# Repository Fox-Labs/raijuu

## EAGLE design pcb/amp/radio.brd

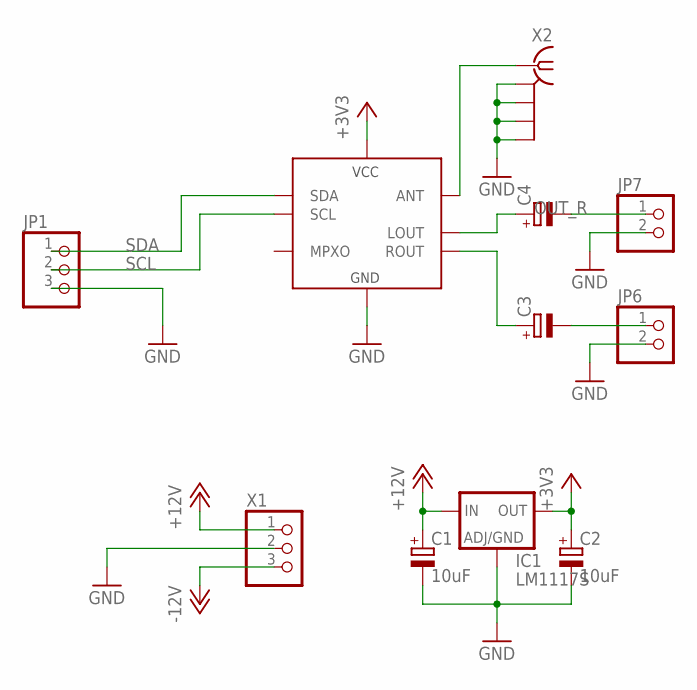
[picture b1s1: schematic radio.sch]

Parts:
C1, C2: 10uF; SMC_A
C3, C4: CPOL-EUD; PANASONIC_D
IC1: LM1117S; SOT223
JP1: PINHD-1X3180; 1X03
JP6, JP7: PINHD-1X2; 1X02
U1: TEA5767
X1: 22-23-2031
X2: BU-SMA-V

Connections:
+3V3: C2.+, IC1.2 (OUT), IC1.4 (OUT), U1.5 (VCC)
+12V: C1.+, IC1.3 (IN), X1.1
-12V: X1.3
GND: C1.-, C2.-, IC1.1 (ADJ), JP1.3, JP6.2, JP7.2, U1.3 (GND), U1.6 (GND), X1.2, X2.2 (GND1), X2.3 (GND2), X2.4 (GND3), X2.5 (GND4)
unnamed: U1.10 (ANT), X2.1
unnamed: C3.+, U1.7 (ROUT)
unnamed: C3.-, JP6.1
unnamed: C4.-, JP7.1
OUT_R: C4.+, U1.8 (LOUT)
SCL: JP1.2, U1.2 (SCL)
SDA: JP1.1, U1.1 (SDA)

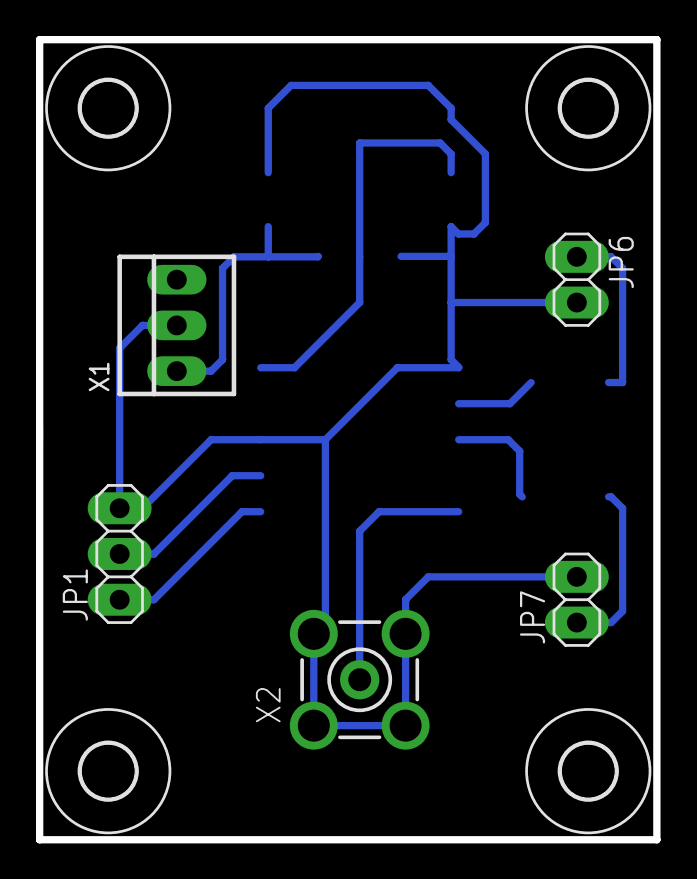
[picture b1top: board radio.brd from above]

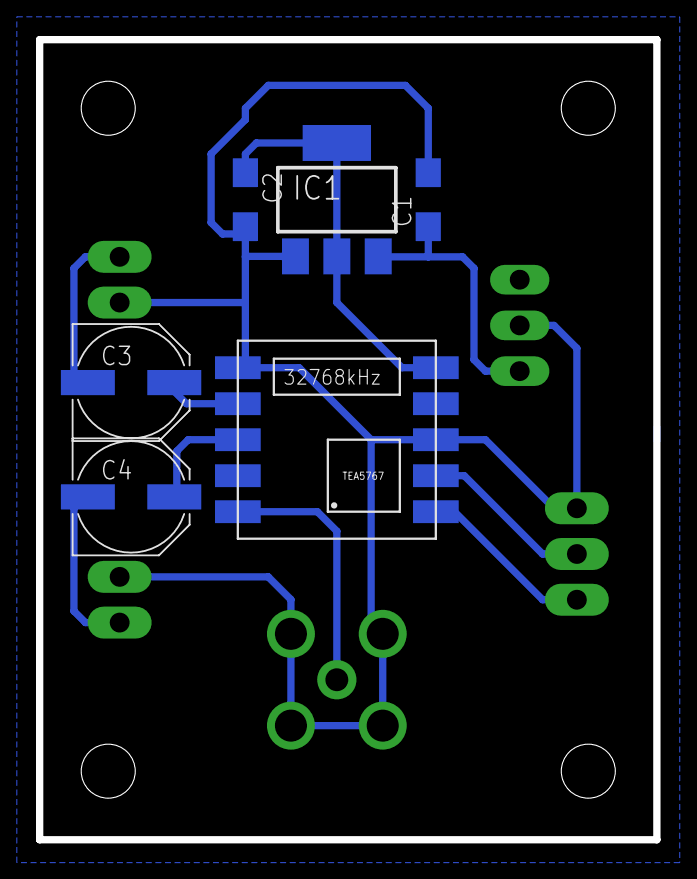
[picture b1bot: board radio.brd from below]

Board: 2 copper layers, 34.3 x 44.5 mm, 15 parts (6 on the bottom side), 10 nets.

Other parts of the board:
U$1, U$2, U$3, U$4: 3,0

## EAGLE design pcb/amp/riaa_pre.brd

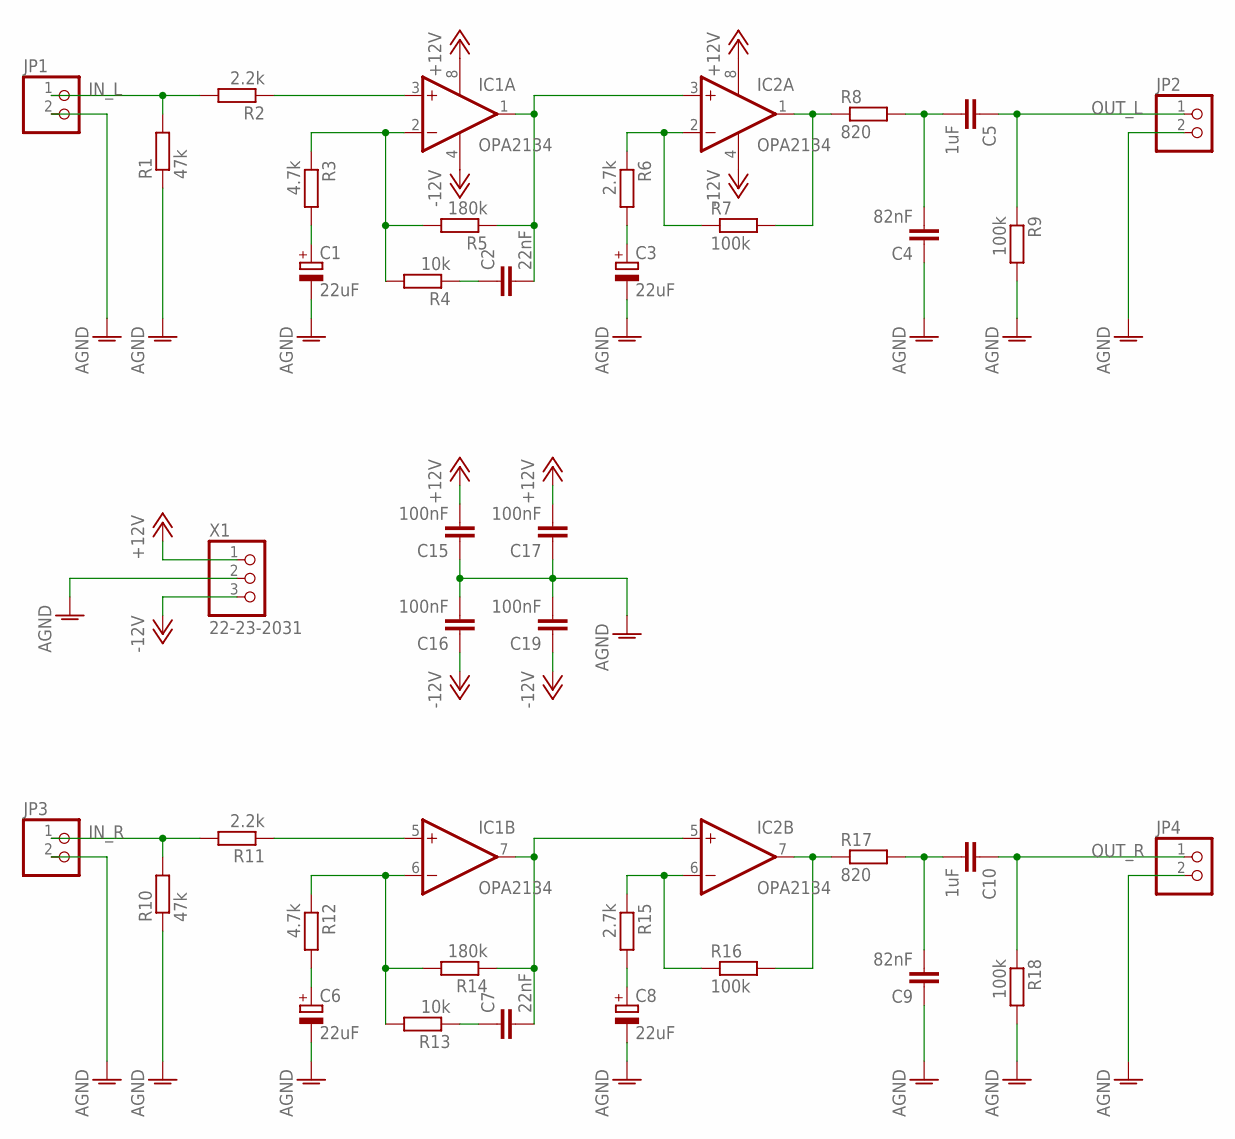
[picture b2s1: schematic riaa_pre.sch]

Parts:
C1, C3, C6, C8: 22uF; E2,5-6
C2, C7: 22nF; C050-025X075
C4, C9: 82nF; C050-025X075
C5, C10: 1uF; C050-045X075
C15, C16, C17, C19: 100nF; C050-025X075
IC1, IC2: OPA2134; DIL08
JP1, JP2, JP3, JP4: PINHD-1X2; 1X02
R1, R10: 47k; 0207/7
R2, R11: 2.2k; 0207/7
R3, R12: 4.7k; 0207/7
R4, R13: 10k; 0207/7
R5, R14: 180k; 0207/7
R6, R15: 2.7k; 0207/7
R7, R9, R16, R18: 100k; 0207/7
R8, R17: 820; 0207/7
X1: 22-23-2031

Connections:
+12V: C15.2, C17.2, IC1.8 (V+), IC2.8 (V+), X1.1
-12V: C16.1, C19.1, IC1.4 (V-), IC2.4 (V-), X1.3
AGND: C1.-, C3.-, C4.1, C6.-, C8.-, C9.1, C15.1, C16.2, C17.1, C19.2, JP1.2, JP2.2, JP3.2, JP4.2, R1.1, R9.2, R10.1, R18.2, X1.2
IN_L: JP1.1, R1.2, R2.2
IN_R: JP3.1, R10.2, R11.2
unnamed: C3.+, R6.2
unnamed: IC1.3 (+IN), R2.1
unnamed: C2.2, IC1.1 (OUT), IC2.3 (+IN), R5.1
unnamed: C4.2, C5.2, R8.2
unnamed: C2.1, R4.1
unnamed: IC1.2 (-IN), R3.1, R4.2, R5.2
unnamed: IC2.6 (-IN), R15.1, R16.1
unnamed: IC2.7 (OUT), R16.2, R17.1
unnamed: IC1.5 (+IN), R11.1
unnamed: C7.2, IC1.7 (OUT), IC2.5 (+IN), R14.1
unnamed: C7.1, R13.1
unnamed: IC1.6 (-IN), R12.1, R13.2, R14.2
unnamed: C6.+, R12.2
unnamed: C8.+, R15.2
unnamed: C9.2, C10.2, R17.2
unnamed: IC2.2 (-IN), R6.1, R7.1
unnamed: IC2.1 (OUT), R7.2, R8.1
unnamed: C1.+, R3.2
OUT_L: C5.1, JP2.1, R9.1
OUT_R: C10.1, JP4.1, R18.1

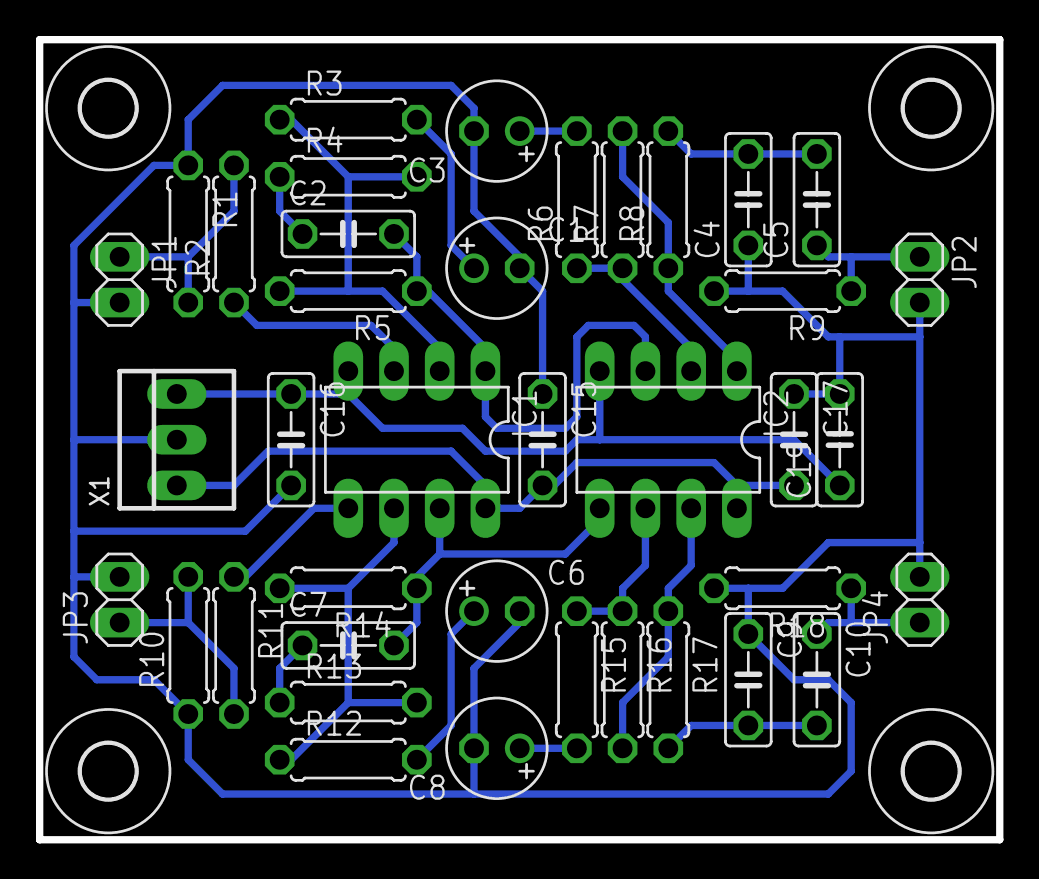
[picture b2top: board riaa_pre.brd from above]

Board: 2 copper layers, 53.3 x 44.5 mm, 43 parts (0 on the bottom side), 25 nets.

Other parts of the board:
U$1, U$2, U$3, U$4: 3,0

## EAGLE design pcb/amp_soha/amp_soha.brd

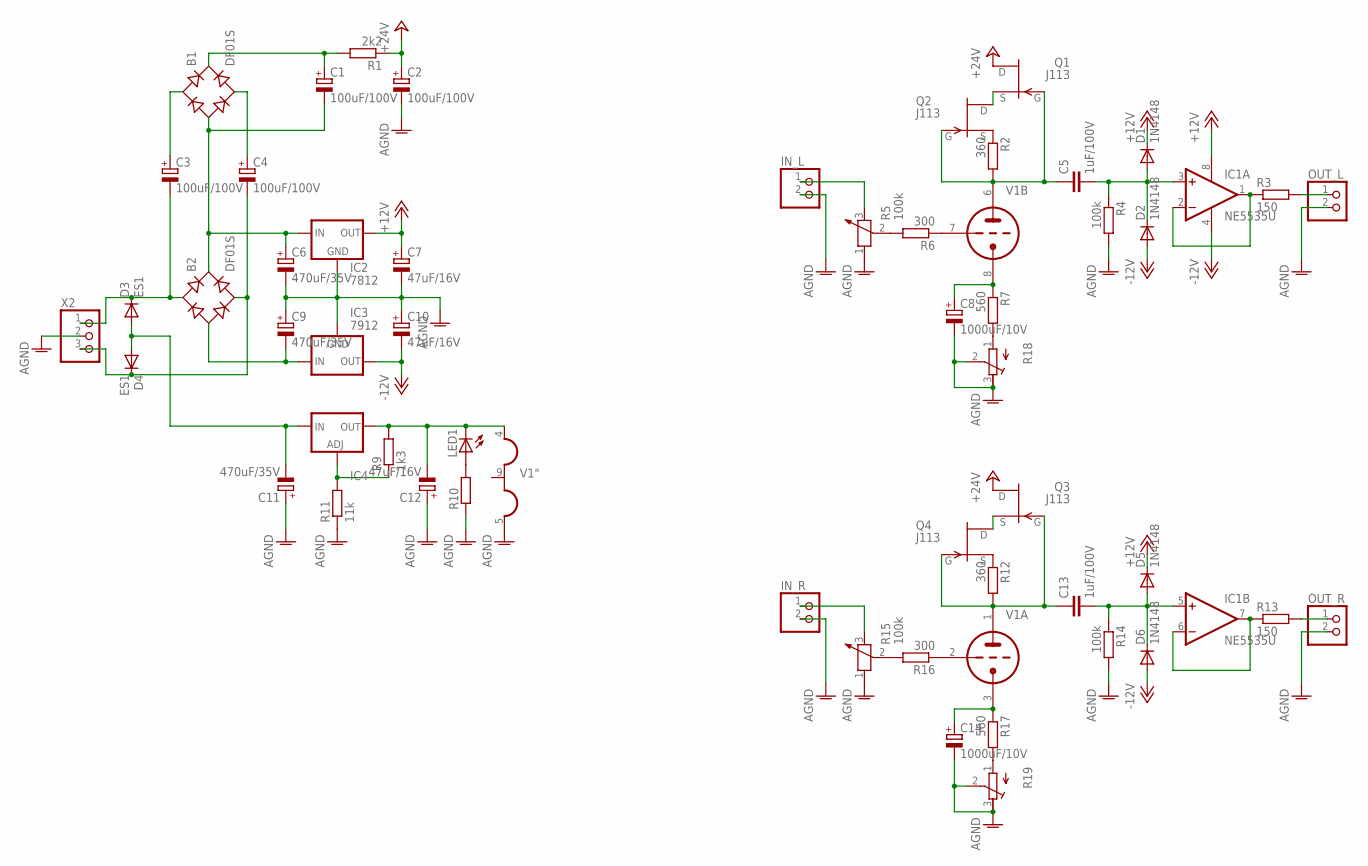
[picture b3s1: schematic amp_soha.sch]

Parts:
B1, B2: DF01S; DFS
C1, C2, C3, C4: 100uF/100V; E5-10,5
C5, C13: 1uF/100V; C075-052X106
C6, C9, C11: 470uF/35V; E5-10,5
C7, C10, C12: 47uF/16V; E2,5-6
C8, C14: 1000uF/10V; E5-10,5
D1, D2, D5, D6: 1N4148; D0805
D3, D4: ES1; DO-214AC
IC1: NE5535U; SO08
IC2: 7812; 78XXS
IC3: 7912; 79XXS
IC4: LM337TS; 337TS
IN_L: PINHD-1X2; 1X02
IN_R: PINHD-1X2; 1X02
LED1: LED5MM
OUT_L: PINHD-1X2; 1X02
OUT_R: PINHD-1X2; 1X02
Q1, Q2, Q3, Q4: J113; TO92
R1: 2k2; R0805
R2, R12: 360; R0805
R3, R13: 150; R0805
R4, R14: 100k; R0805
R5, R15: 100k; 1X03
R6, R16: 300; R0805
R7, R17: 560; R0805
R9: 1k3; R0805
R10: R-EU_; R0805
R11: 11k; R0805
R18, R19: RTRIM329Y; RTRIM3296Y
V1: 12AU7-P; NOVAL
X2: W237-103

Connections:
+12V: C7.+, D1.K (C), D5.K (C), IC1.8 (V+), IC2.OUT
+24V: C2.+, Q1.3 (D), Q3.3 (D), R1.1
-12.6V: C12.-, IC4.3 (OUT), LED1.K (C), R9.2, V1.4 (H1)
-12V: C10.-, D2.A, D6.A, IC1.4 (V-), IC3.OUT
AGND: C2.-, C6.-, C7.-, C8.-, C9.+, C10.+, C11.+, C12.+, C14.-, IC2.GND, IC3.GND, IN_L.2, IN_R.2, OUT_L.2, OUT_R.2, R4.2, R5.1, R10.1, R11.1, R14.2, R15.1, R18.2 (S), R18.3 (E), R19.2 (S), R19.3 (E), V1.5 (H3), X2.2
unnamed: B2.AC1, C3.-, D3.C, X2.1
unnamed: B2.AC2, C4.-, D4.C, X2.3
unnamed: C11.-, D3.A, D4.A, IC4.2 (IN)
unnamed: IC4.1 (ADJ), R9.1, R11.2
unnamed: B2.-, C9.-, IC3.IN
unnamed: B1.-, B2.+, C1.-, C6.+, IC2.IN
unnamed: LED1.A, R10.2
unnamed: B1.AC1, C3.+
unnamed: B1.AC2, C4.+
unnamed: R16.1, V1.2 (TG)
unnamed: B1.+, C1.+, R1.2
unnamed: IN_L.1, R5.3 (2)
unnamed: R5.2 (3), R6.2
unnamed: R6.1, V1.7 (TG)
unnamed: C8.+, R7.1, V1.8 (TK)
unnamed: Q2.2 (S), R2.1
unnamed: R7.2, R18.1 (A)
unnamed: R17.2, R19.1 (A)
unnamed: C5.1, Q1.1 (G), Q2.1 (G), R2.2, V1.6 (TA)
unnamed: Q1.2 (S), Q2.3 (D)
unnamed: C5.2, D1.A, D2.K (C), IC1.3 (+IN), R4.1
unnamed: IC1.1 (OUT), IC1.2 (-IN), R3.1
unnamed: OUT_L.1, R3.2
unnamed: IN_R.1, R15.3 (2)
unnamed: R15.2 (3), R16.2
unnamed: C14.+, R17.1, V1.3 (TK)
unnamed: C13.1, Q3.1 (G), Q4.1 (G), R12.2, V1.1 (TA)
unnamed: Q4.2 (S), R12.1
unnamed: Q3.2 (S), Q4.3 (D)
unnamed: C13.2, D5.A, D6.K (C), IC1.5 (+IN), R14.1
unnamed: IC1.6 (-IN), IC1.7 (OUT), R13.1
unnamed: OUT_R.1, R13.2

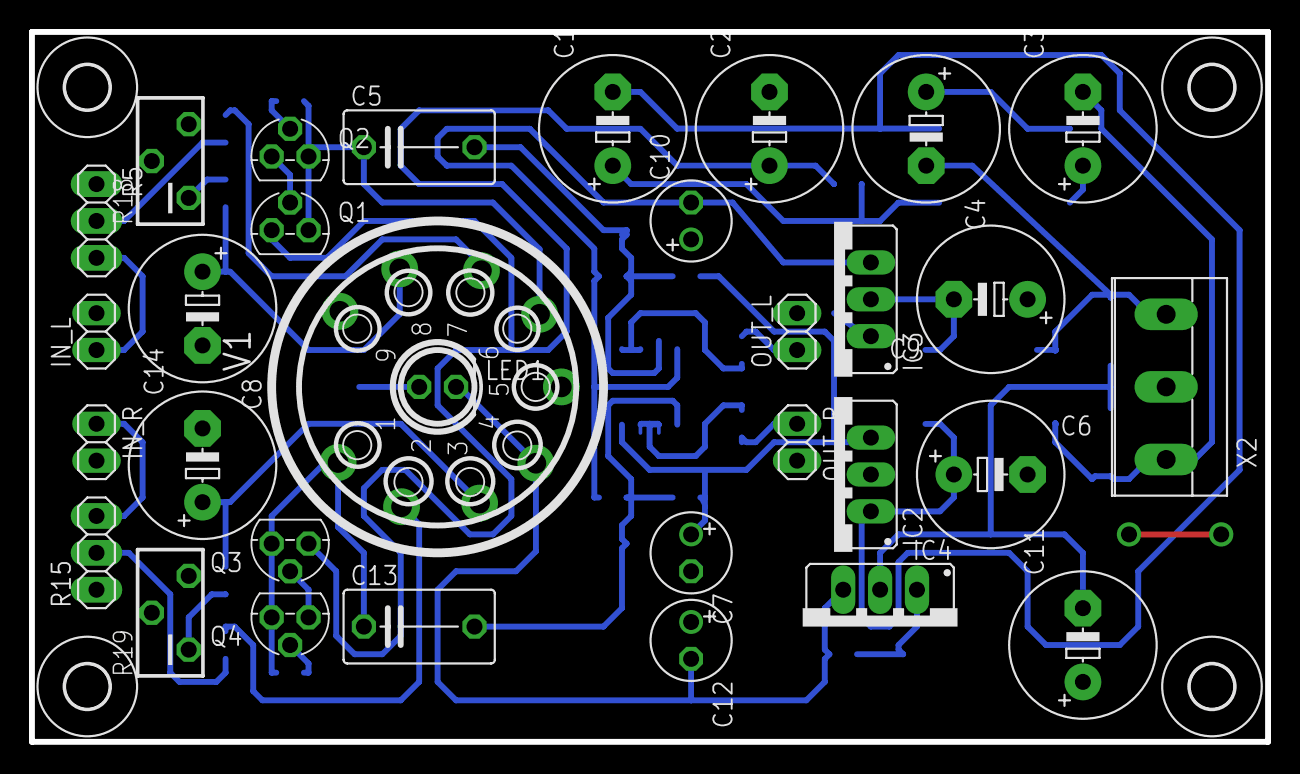
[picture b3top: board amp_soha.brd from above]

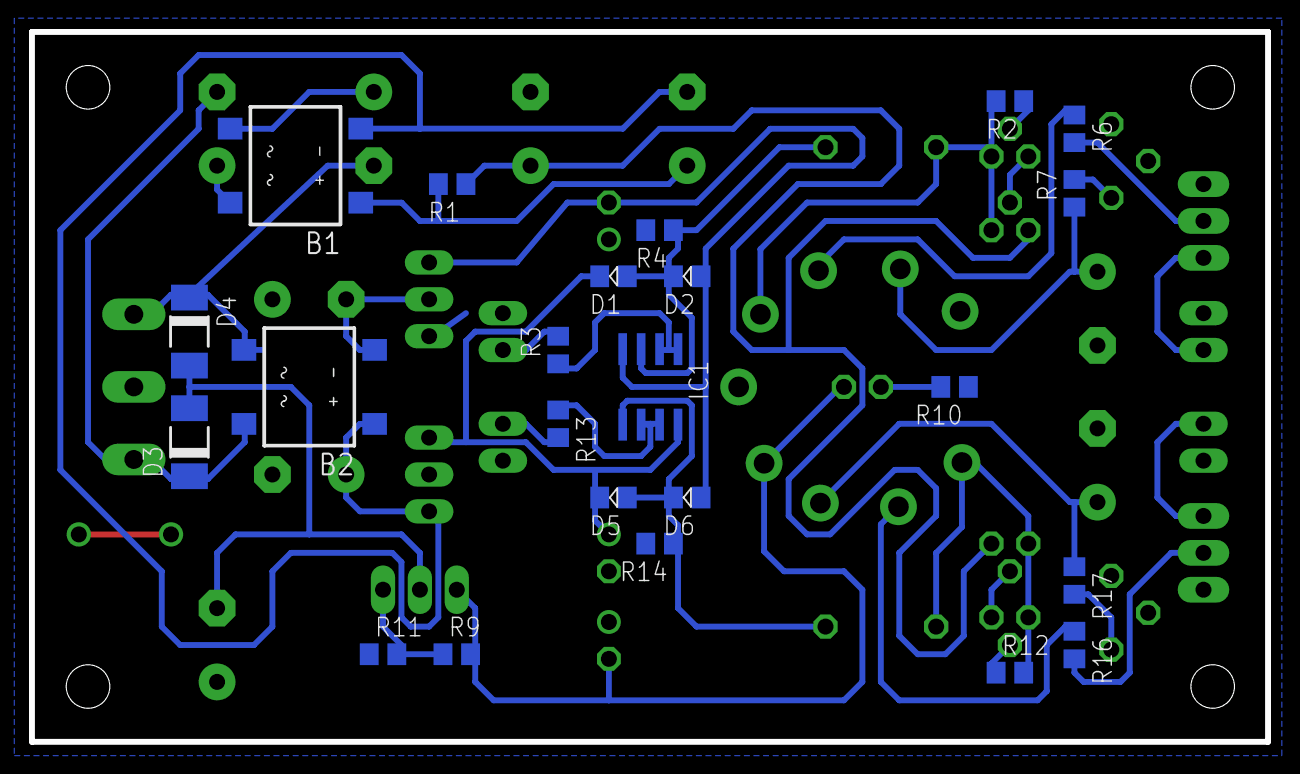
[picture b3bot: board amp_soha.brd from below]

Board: 2 copper layers, 85.1 x 48.9 mm, 59 parts (23 on the bottom side), 37 nets.

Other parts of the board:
U$1, U$2, U$3, U$4: 3,0
